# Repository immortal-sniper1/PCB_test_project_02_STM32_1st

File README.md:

# PCB_test_project_02_STM32_1st
 1st STM32 PCB project so sensors and open gpio +power

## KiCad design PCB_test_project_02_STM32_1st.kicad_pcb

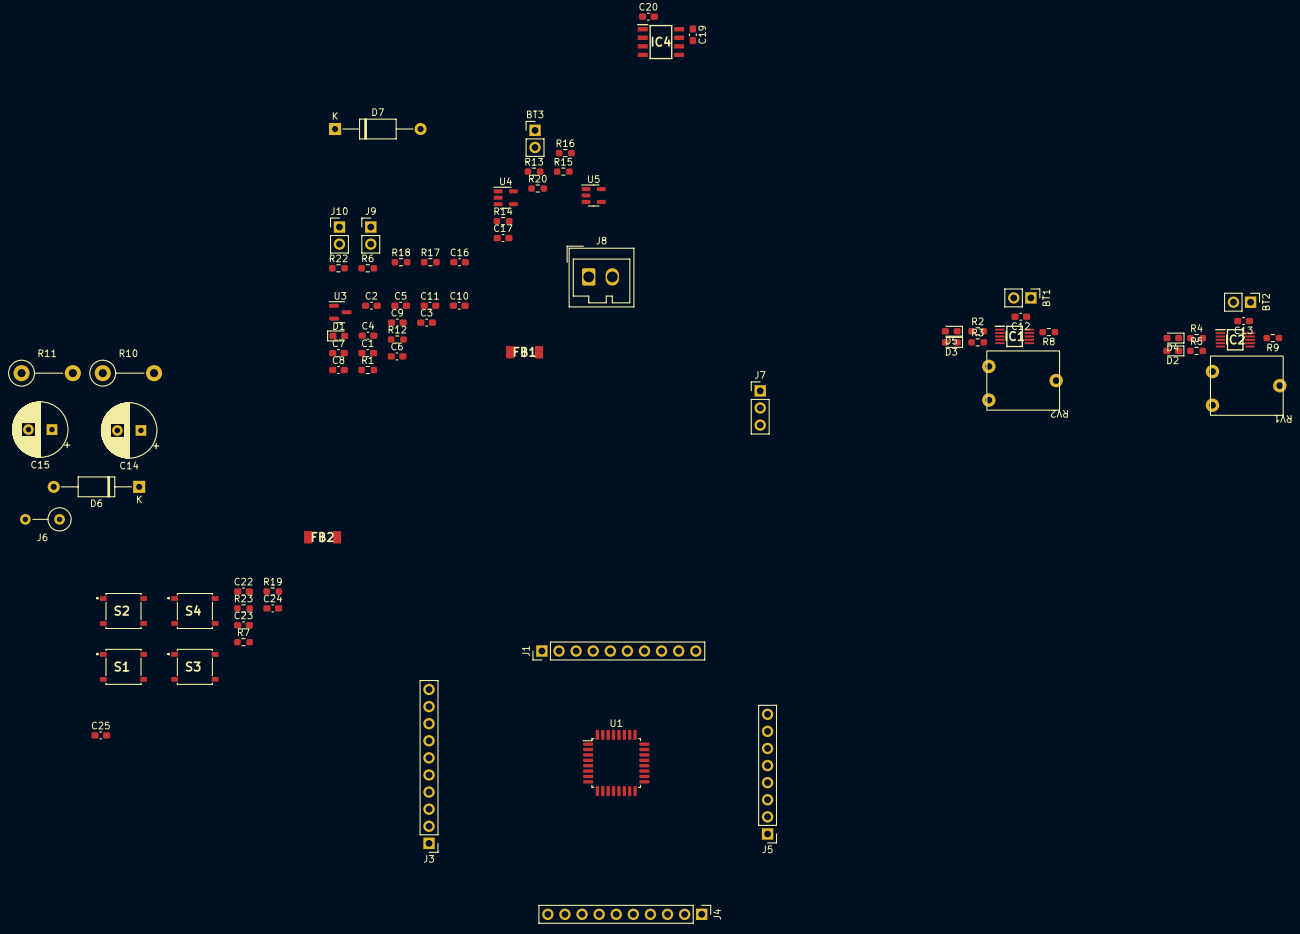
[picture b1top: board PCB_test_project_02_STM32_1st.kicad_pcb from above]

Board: 2 copper layers, 79 parts (0 on the bottom side), 61 nets, no tracks yet.

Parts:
BT1, BT2, BT3: Battery_Cell; PinHeader_1x02_P2.54mm_Vertical
C1, C6, C7, C8: 10n; C_0603_1608Metric_Pad1.08x0.95mm_HandSolder
C2, C5: 24P; C_0603_1608Metric_Pad1.08x0.95mm_HandSolder
C3, C4, C22, C23, C24, C25: 100n; C_0603_1608Metric_Pad1.08x0.95mm_HandSolder
C9, C10, C16, C17, C19, C20: 1u; C_0603_1608Metric_Pad1.08x0.95mm_HandSolder
C11: C_Small; C_0603_1608Metric_Pad1.08x0.95mm_HandSolder
C12, C13: 4.7u; C_0603_1608Metric_Pad1.08x0.95mm_HandSolder
C14, C15: 3.3; CP_Radial_D8.0mm_P3.50mm
D1, D2, D3, D4, D5: LED_Small; LED_0603_1608Metric_Pad1.05x0.95mm_HandSolder
D6, D7: D_Shockley; D_A-405_P12.70mm_Horizontal
FB1, FB2: HI1806T600R-10; BEADC4516X185N
IC1, IC2: MCP73834T-FCI_UN; SOP50P490X110-10N
IC4: AP2112M-3.3TRG1; SOIC127P600X170-8N
J1, J3, J4: Conn_01x10; PinHeader_1x10_P2.54mm_Vertical
J5: Conn_01x08; PinHeader_1x08_P2.54mm_Vertical
J6: Conn_01x02; R_Axial_DIN0309_L9.0mm_D3.2mm_P5.08mm_Vertical
J7: Conn_01x03; PinHeader_1x03_P2.54mm_Vertical
J8: Conn_01x02; Wago_734-132_1x02_P3.50mm_Vertical
J9, J10: Conn_01x02; PinHeader_1x02_P2.54mm_Vertical
R1, R12: 1k; R_0603_1608Metric_Pad0.98x0.95mm_HandSolder
R2, R3, R4, R5: 470; R_0603_1608Metric_Pad0.98x0.95mm_HandSolder
R6, R7, R8, R9, R14, R15, R19, R22, R23: 10k; R_0603_1608Metric_Pad0.98x0.95mm_HandSolder
R10, R11: 1M; R_Axial_DIN0411_L9.9mm_D3.6mm_P7.62mm_Vertical
R13: 47k; R_0603_1608Metric_Pad0.98x0.95mm_HandSolder
R16, R20: 5m; R_0603_1608Metric_Pad0.98x0.95mm_HandSolder
R17: 1m; R_0603_1608Metric_Pad0.98x0.95mm_HandSolder
R18: 50k; R_0603_1608Metric_Pad0.98x0.95mm_HandSolder
RV1, RV2: 4.7k; 2002102255
S1, S2, S3, S4: PTS526_SK15_SMTR2_LFS; PTS526SK15SMTR2LFS
U1: STM32L011K4Tx; LQFP-32_7x7mm_P0.8mm
U3: LM4040DBZ-3; SOT-23
U4, U5: OP179GRT; SOT-23-5

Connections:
+3.3VA: C8.1, C9.1, FB1.2, R12.1, U1.5 (VDDA)
+5V: C11.1, D1.2 (A), D2.2 (A), D3.2 (A), D4.2 (A), D5.2 (A), D7.2 (A), FB2.2, IC1.1 (VDD_1), IC1.2 (VDD_2), IC2.1 (VDD_1), IC2.2 (VDD_2), IC4.5 (EN), J1.9, J1.10, R22.1
/NRST: J3.10, J5.2, S1.3 (NO_1), S1.4 (NO_2), U1.4 (NRST)
/osc_in: C2.2, U1.2 (PC14)
/osc_out: C5.2, U1.3 (PC15)
/power_USB_BATT/LDO: C20.1, IC4.1 (VOUT)
ADC1: BT1.1 (+), C12.1, IC1.9 (VBAT_1), IC1.10 (VBAT_2), J7.1, U1.9 (PA3)
ADC2: BT2.1 (+), C13.1, IC2.9 (VBAT_1), IC2.10 (VBAT_2), J7.3, U1.10 (PA4)
ADC3: R16.1, R20.2, U1.11 (PA5)
ADC4: R12.2, U1.12 (PA6), U3.1 (K)
GND: BT1.2 (-), BT2.2 (-), BT3.2 (-), C1.2, C2.1, C3.1, C4.2, C5.1, C6.2, C7.2, C8.2, C9.2, C10.2, C11.2, C12.2, C13.2, C15.2, C16.2, C17.1, C19.2, C20.2, C22.1, C23.1, C24.1, C25.2, IC1.5 (VSS), IC2.5 (VSS), IC4.6 (GND_1), IC4.7 (GND_2), J1.3, J1.8, J3.3, J3.7, J3.8, J4.1, J4.6, J5.1, J5.7, J6.2, J7.2, J8.1, J9.2, J10.2, R1.2, R8.1, R9.1, R11.1, R13.2, R16.2, R17.2, R22.2, RV1.2, RV2.2, U1.16 (VSS), U1.32 (VSS), U3.2 (A), U4.5 (V-), U5.5 (V-)
I2C_CLK: J3.4, U1.29 (PB6)
I2C_SDA: J3.5, U1.30 (PB7)
unnamed: BT3.1 (+), J8.2, R20.1
unnamed: C3.2, S1.1 (COM_1), S1.2 (COM_2)
unnamed: C14.1, D6.1 (K), J6.1, R10.2
unnamed: C14.2, C15.1, R10.1, R11.2
unnamed: C16.1, R14.1, U4.3 (+)
unnamed: C17.2, R6.1, U5.3 (+)
unnamed: C19.1, IC4.8 (VIN)
unnamed: C22.2, S2.1 (COM_1), S2.2 (COM_2)
unnamed: C23.2, S3.1 (COM_1), S3.2 (COM_2)
unnamed: C24.2, S4.1 (COM_1), S4.2 (COM_2)
unnamed: D1.1 (K), R1.1
unnamed: D2.1 (K), R2.1
unnamed: D3.1 (K), R3.1
unnamed: D4.1 (K), R4.1
unnamed: D5.1 (K), R5.1
unnamed: IC1.3 (STAT1), R2.2
unnamed: IC1.4 (STAT2), R3.2
unnamed: IC1.6 (PROG), RV2.1
unnamed: IC1.8 (THERM), R8.2
unnamed: IC2.3 (STAT1), R4.2
unnamed: IC2.4 (STAT2), R5.2
unnamed: IC2.6 (PROG), RV1.1
unnamed: IC2.8 (THERM), R9.2
unnamed: J9.1, RV2.3
unnamed: J10.1, RV1.3
unnamed: R18.1, U5.1
unnamed: R6.2, U4.1
unnamed: R15.1, R18.2, U5.4 (-)
OpAmp_power: C1.1, C4.1, C6.1, C7.1, C10.1, C25.1, FB1.1, J1.1, J1.2, J5.8, R7.2, R19.2, R23.2, U1.1 (VDD), U1.17 (VDD), U4.2 (V+), U5.2 (V+)
PA1: J4.10, U1.7 (PA1)
PA2: J4.9, U1.8 (PA2)
PA7: J4.3, U1.13 (PA7)
PB0: R7.1, S2.3 (NO_1), S2.4 (NO_2), U1.14 (PB0)
PB1: R23.1, S4.3 (NO_1), S4.4 (NO_2), U1.15 (PB1)
PB9: R19.1, S3.3 (NO_1), S3.4 (NO_2), U1.31 (PB9)
RCC_MCO_clk: J3.9, U1.18 (PA8)
SDW_DO: J3.1, U1.24 (PA14)
SPI_CLK: J1.6, U1.26 (PB3)
SPI_MISO: J1.5, U1.27 (PB4)
SPI_MOSI: J1.4, U1.28 (PB5)
SPI_SS: J1.7, U1.25 (PA15)
SWD_CLK: J3.2, U1.23 (PA13)
UART_CTS: J5.5, U1.21 (PA11)
UART_RTS: J5.6, U1.22 (PA12)
UART_RX: J5.4, U1.20 (PA10)
UART_TX: J5.3, U1.19 (PA9)
test_pwm: R13.1, R14.2
wakeup1: J3.6, U1.6 (PA0)

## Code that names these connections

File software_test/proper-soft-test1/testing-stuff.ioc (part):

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Mcu.Name=STM32L010K4Tx
Mcu.Package=LQFP32
Mcu.UserName=STM32L010K4Tx
PA0-CK_IN.Mode=SYS_WakeUp0
PA0-CK_IN.Signal=SYS_WKUP1
PA10.Mode=Asynchronous
PA10.Signal=USART2_RX
PA11.Mode=CTS_RTS
PA11.Signal=USART2_CTS
PA12.Mode=CTS_RTS
PA12.Signal=USART2_RTS
PA13.Mode=Serial_Wire
PA13.Signal=SYS_SWDIO
PA14.Mode=Serial_Wire
PA14.Signal=SYS_SWCLK
PA15.Mode=NSS_Signal_Hard_Output
PA15.Signal=SPI1_NSS
PA3.Mode=IN3
PA3.Signal=ADC_IN3
PA4.Mode=IN4
PA4.Signal=ADC_IN4
PA5.Mode=IN5
PA5.Signal=ADC_IN5
PA6.Mode=IN6
PA6.Signal=ADC_IN6
PA7.Mode=IN7
PA7.Signal=ADC_IN7
PA8.Mode=Clock-out
PA8.Signal=RCC_MCO
PA9.Mode=Asynchronous
PA9.Signal=USART2_TX
PB3.Mode=Full_Duplex_Master
PB3.Signal=SPI1_SCK
PB4.Mode=Full_Duplex_Master
PB4.Signal=SPI1_MISO
PB5.Mode=Full_Duplex_Master
PB5.Signal=SPI1_MOSI
PB6.Mode=I2C
PB6.Signal=I2C1_SCL
PB7.Mode=I2C
PB7.Signal=I2C1_SDA
PC14-OSC32_IN.Mode=LSE-External-Oscillator
PC14-OSC32_IN.Signal=RCC_OSC32_IN
PC15-OSC32_OUT.Mode=LSE-External-Oscillator
PC15-OSC32_OUT.Signal=RCC_OSC32_OUT
RCC.HSE_VALUE=4000000
RCC.SYSCLKFreq_VALUE=2097000
board=custom
